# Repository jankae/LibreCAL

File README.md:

# LibreCAL
**4-port, 9kHz to 6GHz eCal module for VNAs**

## Quick Start
* You can find released versions of the GUI application and the device firmware [here](https://github.com/jankae/LibreCAL/releases).
* You do *not* need the LibreCAL-GUI if you are controlling the device manually, via a script or through the [LibreVNA-GUI](https://github.com/jankae/LibreVNA).
* If you would like to try out the newest features, the compiled versions of each commit can be found [here](https://github.com/jankae/LibreCAL/actions) (but keep in mind that some features might be unstable or incomplete).
* Please see the [user manual](Documentation/manual.pdf) for details of operation.
* If you would like to control the LibreCAL with a script, see the [SCPI API](Documentation/SCPI_API.pdf).

## Factory calibration
* All LibreCAL devices are preprogrammed with individually measured factory calibration coefficients (if you build one yourself, you need a way to measure them)
* These coefficients are important, without them the LibreCAL is nothing more than an ordinary RF switch matrix
* If the coefficients have been lost, you can download them [here](https://librecal.kaeberich.com/) (based on the serial number of your LibreCAL). If no coefficients for your LibreCAL are available, it could be a clone (not produced through official channels)

## Installation

All of the following steps are only required if you plan to use the LibreCAL-GUI. If you plan to control the LibreCAL manually with the buttons, through a script or the LibreVNA-GUI, there is no need to download the LibreCAL-GUI (but you should still install the udev rule on Linux systems).

### Windows
* Download the latest [Release](https://github.com/jankae/LibreCAL/releases) and unpack the zip file
* Start the included LibreCAL-GUI.exe
* No installation or driver is required, simply move the extracted folder somewhere convenient

### Ubuntu
* Download the latest [Release](https://github.com/jankae/LibreCAL/releases) and unpack the zip file
* Install the required libraries:
```console
sudo apt install libqt6widgets6 libqt6charts6 libqt6svg6
```
* Install the udev rule (otherwise you don't have the permissions to access the USB device):
```console
wget https://raw.githubusercontent.com/jankae/LibreCAL/main/Software/52-LibreCAL.rules
sudo cp 52-LibreCAL.rules /etc/udev/rules.d
```
* Either reboot or reload the udev rules manually:
```console
sudo udevadm control --reload-rules
sudo udevadm trigger
```
* You can now start GUI:
```console
cd $UNPACKED_ZIP_FOLDER$
./LibreCAL-GUI
```

### MacOS
* Download the latest [Release](https://github.com/jankae/LibreCAL/releases)
  * If you are using MacOS 14+ use the release with `latest` in the name.
  * If you are using MacOS >13.7 use the release with  `13.7` in the name.
* Unpack the zip file and move LibreCAL-GUI.app to your `/Applications` folder.
* Start LibreCAL-GUI.app and add a security exception to allow the Mac to run the app with an "untrusted" signing key.
* Launch app again.

## How does it work?
The LibreCAL is just a switch-matrix with additional options to terminate each port into an open, short or 50 Ohm connection:

While the blockdiagram is small and simple, the tricky part of any eCal module is repeatability. The LibreCAL contains an integrated heater and temperature sensor to keep the critical parts at a constant temperature during operation. Furthermore, high quality SMA connectors are used to ensure good return loss.

The coefficients of the calibration standards are stored in standard touchstone format on the device. They must be measured and written once after assembling the PCB and housing.

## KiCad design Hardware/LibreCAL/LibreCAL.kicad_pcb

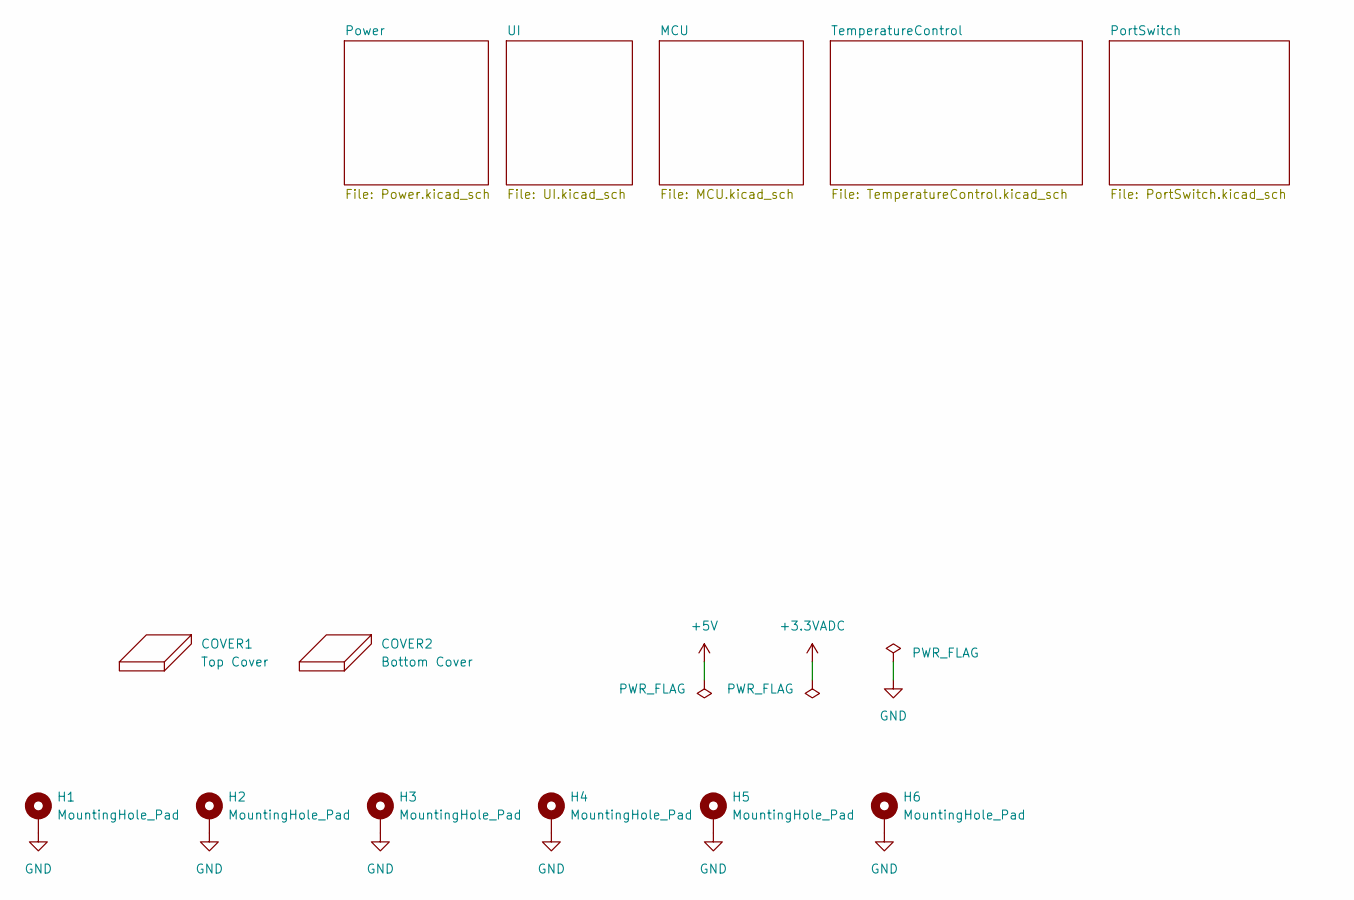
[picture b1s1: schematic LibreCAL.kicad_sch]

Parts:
COVER1: Top Cover; TopCover; LCSC_Part NA
COVER2: Bottom Cover; BottomCover; LCSC_Part NA
H1, H2, H3, H4, H5, H6: MountingHole_Pad; MountingHole_3.2mm_M3_ISO14580_Pad_TopBottom; LCSC_Part NA

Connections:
GND: H1.1, H2.1, H3.1, H4.1, H5.1, H6.1; also elsewhere on the board

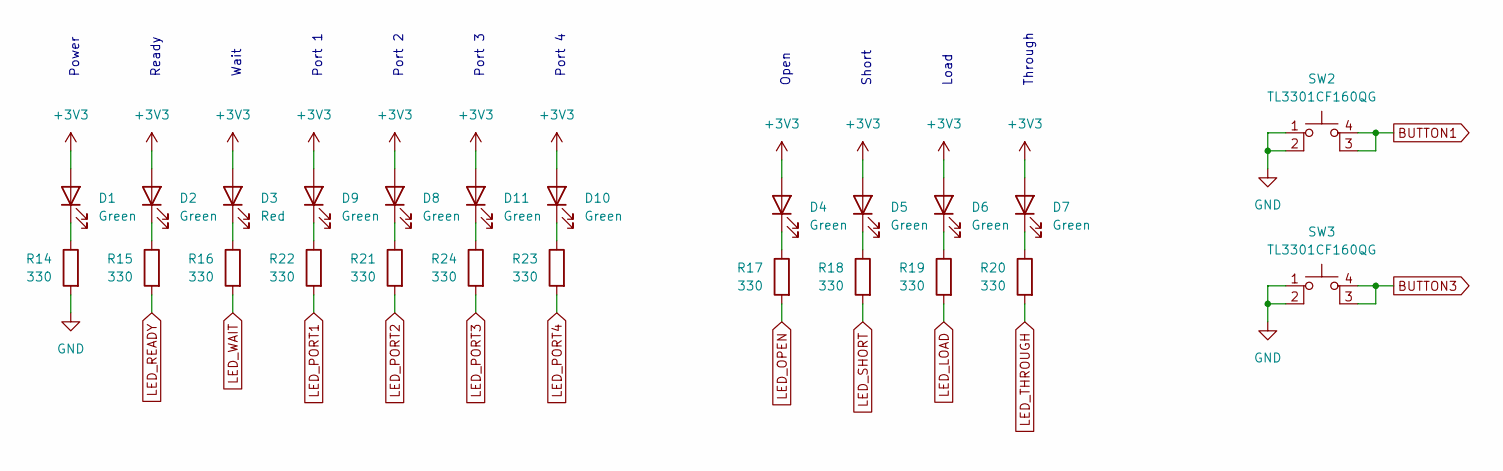
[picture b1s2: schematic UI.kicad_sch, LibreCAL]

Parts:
D1, D2, D4, D5, D6, D7, D8, D9, D10, D11: Green; LED_0603_1608Metric; LCSC_Part C72043
D3: Red; LED_0603_1608Metric; LCSC_Part C93128
R14, R15, R16, R17, R18, R19, R20, R21, R22, R23, R24: 330; R_0402_1005Metric; LCSC_Part C25104
SW2, SW3: TL3301CF160QG; TL3301C-J; LCSC_Part C273522

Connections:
+3V3: D1.2 (A), D2.2 (A), D3.2 (A), D4.2 (A), D5.2 (A), D6.2 (A), D7.2 (A), D8.2 (A), D9.2 (A), D10.2 (A), D11.2 (A); also elsewhere on the board
BUTTON1: SW2.3 (K), SW2.4 (A); also elsewhere on the board
BUTTON3: SW3.3 (K), SW3.4 (A); also elsewhere on the board
GND: R14.2, SW2.1, SW2.2, SW3.1, SW3.2; also elsewhere on the board
LED_LOAD: R19.2; also elsewhere on the board
LED_OPEN: R17.2; also elsewhere on the board
LED_PORT1: R22.2; also elsewhere on the board
LED_PORT2: R21.2; also elsewhere on the board
LED_PORT3: R24.2; also elsewhere on the board
LED_PORT4: R23.2; also elsewhere on the board
LED_READY: R15.2; also elsewhere on the board
LED_SHORT: R18.2; also elsewhere on the board
LED_THROUGH: R20.2; also elsewhere on the board
LED_WAIT: R16.2; also elsewhere on the board
unnamed: D1.1 (K), R14.1
unnamed: D2.1 (K), R15.1
unnamed: D3.1 (K), R16.1
unnamed: D4.1 (K), R17.1
unnamed: D5.1 (K), R18.1
unnamed: D6.1 (K), R19.1
unnamed: D7.1 (K), R20.1
unnamed: D8.1 (K), R21.1
unnamed: D9.1 (K), R22.1
unnamed: D10.1 (K), R23.1
unnamed: D11.1 (K), R24.1

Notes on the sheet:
Short
Port 3
Power
Port 1
Through
Wait
Port 2
Ready
Open
Load
Port 4

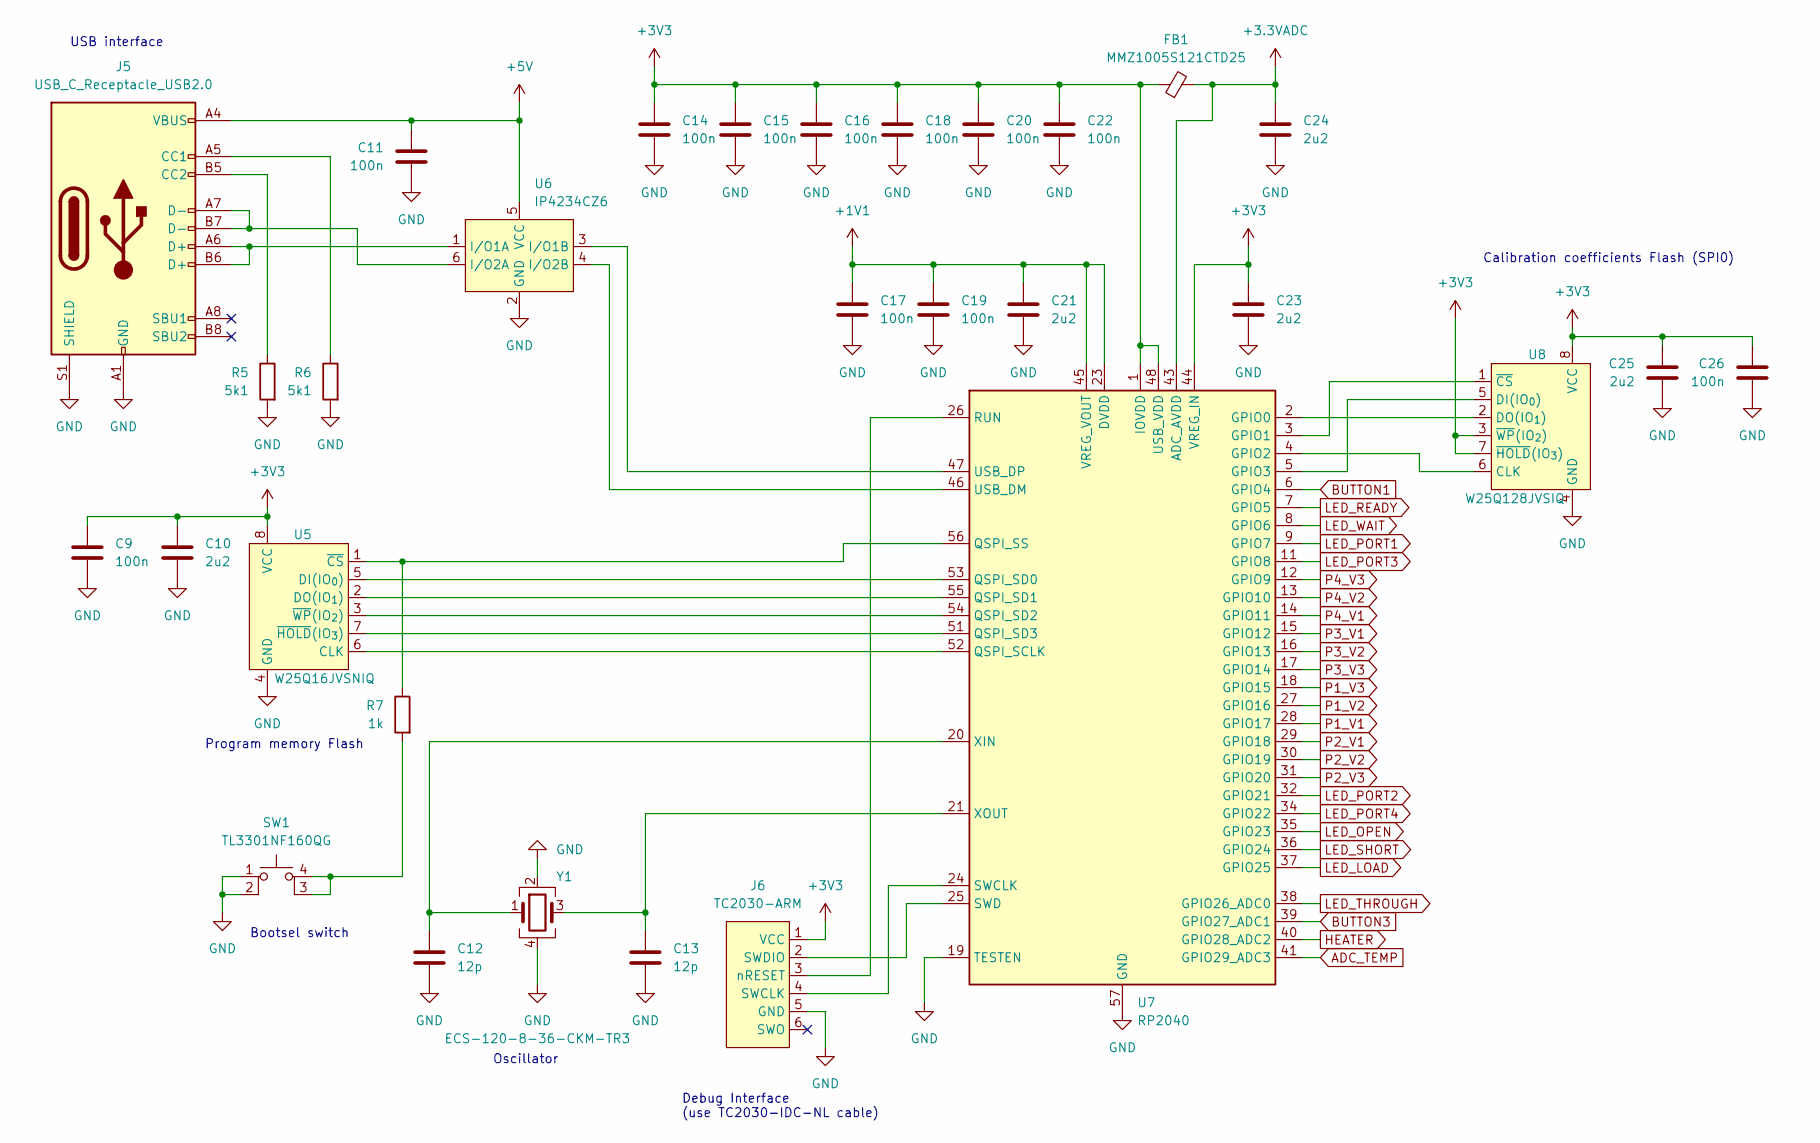
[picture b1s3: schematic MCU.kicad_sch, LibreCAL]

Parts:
C9, C11, C14, C15, C16, C17, C18, C19, C20, C22, C26: 100n; C_0402_1005Metric; LCSC_Part C307331
C10, C21, C23, C24, C25: 2u2; C_0402_1005Metric; LCSC_Part C307418
C12, C13: 12p; C_0402_1005Metric; LCSC_Part C76948
FB1: MMZ1005S121CTD25; L_0402_1005Metric; LCSC_Part C404693
J5: USB_C_Receptacle_USB2.0; USB_C_Receptacle_HRO_TYPE-C-31-M-12; LCSC_Part C165948
J6: TC2030-ARM; Tag-Connect_TC2030-IDC-NL_2x03_P1.27mm_Vertical; LCSC_Part NA
R5, R6: 5k1; R_0402_1005Metric; LCSC_Part C105872
R7: 1k; R_0402_1005Metric; LCSC_Part C106235
SW1: TL3301NF160QG; TL3301N-J; LCSC_Part C273527
U5: W25Q16JVSNIQ; SOIC-8_3.9x4.9mm_P1.27mm; LCSC_Part C115407
U6: IP4234CZ6; SOT-23-6; LCSC_Part C455086
U7: RP2040; LCSC_Part C2040
U8: W25Q128JVSIQ; SOIC-8_5.23x5.23mm_P1.27mm; LCSC_Part C115407
Y1: ECS-120-8-36-CKM-TR3; Crystal_SMD_2520-4Pin_2.5x2.0mm; LCSC_Part C5349079

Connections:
+1V1: C17.1, C19.1, C21.1, U7.23 (DVDD), U7.45 (VREG_VOUT), U7.50 (DVDD)
+3.3VADC: C24.1, FB1.2, U7.43 (ADC_AVDD); also elsewhere on the board
+3V3: C9.1, C10.1, C14.1, C15.1, C16.1, C18.1, C20.1, C22.1, C23.1, C25.1, C26.1, FB1.1, J6.1 (VCC), U5.8 (VCC), U7.1 (IOVDD), U7.10 (IOVDD), U7.22 (IOVDD), U7.33 (IOVDD), U7.42 (IOVDD), U7.44 (VREG_IN), U7.48 (USB_VDD), U7.49 (IOVDD), U8.3 (~WP(IO_{2})), U8.7 (~HOLD(IO_{3})), U8.8 (VCC); also elsewhere on the board
+5V: C11.1, J5.A4 (VBUS), J5.A9 (VBUS), J5.B4 (VBUS), J5.B9 (VBUS), U6.5 (VCC); also elsewhere on the board
ADC_TEMP: U7.41 (GPIO29_ADC3); also elsewhere on the board
BUTTON1: U7.6 (GPIO4); also elsewhere on the board
BUTTON3: U7.39 (GPIO27_ADC1); also elsewhere on the board
GND: C9.2, C10.2, C11.2, C12.2, C13.2, C14.2, C15.2, C16.2, C17.2, C18.2, C19.2, C20.2, C21.2, C22.2, C23.2, C24.2, C25.2, C26.2, J5.A1 (GND), J5.A12 (GND), J5.B1 (GND), J5.B12 (GND), J5.S1 (SHIELD), J6.5 (GND), R5.2, R6.2, SW1.1, SW1.2, U5.4 (GND), U6.2 (GND), U7.19 (TESTEN), U7.57 (GND), U8.4 (GND), Y1.2, Y1.4; also elsewhere on the board
HEATER: U7.40 (GPIO28_ADC2); also elsewhere on the board
LED_LOAD: U7.37 (GPIO25); also elsewhere on the board
LED_OPEN: U7.35 (GPIO23); also elsewhere on the board
LED_PORT1: U7.9 (GPIO7); also elsewhere on the board
LED_PORT2: U7.32 (GPIO21); also elsewhere on the board
LED_PORT3: U7.11 (GPIO8); also elsewhere on the board
LED_PORT4: U7.34 (GPIO22); also elsewhere on the board
LED_READY: U7.7 (GPIO5); also elsewhere on the board
LED_SHORT: U7.36 (GPIO24); also elsewhere on the board
LED_THROUGH: U7.38 (GPIO26_ADC0); also elsewhere on the board
LED_WAIT: U7.8 (GPIO6); also elsewhere on the board
unnamed: J5.A5 (CC1), R6.1
unnamed: J5.B5 (CC2), R5.1
unnamed: J6.4 (SWCLK), U7.24 (SWCLK)
unnamed: J6.2 (SWDIO), U7.25 (SWD)
unnamed: J6.3 (nRESET), U7.26 (RUN)
unnamed: R7.2, SW1.3 (K), SW1.4 (A)
unnamed: U5.6 (CLK), U7.52 (QSPI_SCLK)
unnamed: U5.5 (DI(IO_{0})), U7.53 (QSPI_SD0)
unnamed: U5.2 (DO(IO_{1})), U7.55 (QSPI_SD1)
unnamed: R7.1, U5.1 (~CS), U7.56 (QSPI_SS)
unnamed: U5.7 (~HOLD(IO_{3})), U7.51 (QSPI_SD3)
unnamed: U5.3 (~WP(IO_{2})), U7.54 (QSPI_SD2)
unnamed: J5.A6 (D+), J5.B6 (D+), U6.1 (I/O1A)
unnamed: U6.3 (I/O1B), U7.47 (USB_DP)
unnamed: J5.A7 (D-), J5.B7 (D-), U6.6 (I/O2A)
unnamed: U6.4 (I/O2B), U7.46 (USB_DM)
unnamed: U7.2 (GPIO0), U8.2 (DO(IO_{1}))
unnamed: U7.3 (GPIO1), U8.1 (~CS)
unnamed: U7.4 (GPIO2), U8.6 (CLK)
unnamed: U7.5 (GPIO3), U8.5 (DI(IO_{0}))
unnamed: C12.1, U7.20 (XIN), Y1.1
unnamed: C13.1, U7.21 (XOUT), Y1.3
P1_V1: U7.28 (GPIO17); also elsewhere on the board
P1_V2: U7.27 (GPIO16); also elsewhere on the board
P1_V3: U7.18 (GPIO15); also elsewhere on the board
P2_V1: U7.29 (GPIO18); also elsewhere on the board
P2_V2: U7.30 (GPIO19); also elsewhere on the board
P2_V3: U7.31 (GPIO20); also elsewhere on the board
P3_V1: U7.15 (GPIO12); also elsewhere on the board
P3_V2: U7.16 (GPIO13); also elsewhere on the board
P3_V3: U7.17 (GPIO14); also elsewhere on the board
P4_V1: U7.14 (GPIO11); also elsewhere on the board
P4_V2: U7.13 (GPIO10); also elsewhere on the board
P4_V3: U7.12 (GPIO9); also elsewhere on the board

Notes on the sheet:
USB interface
Oscillator
Program memory Flash
Debug Interface (use TC2030-IDC-NL cable)
Bootsel switch
Calibration coefficients Flash (SPI0)

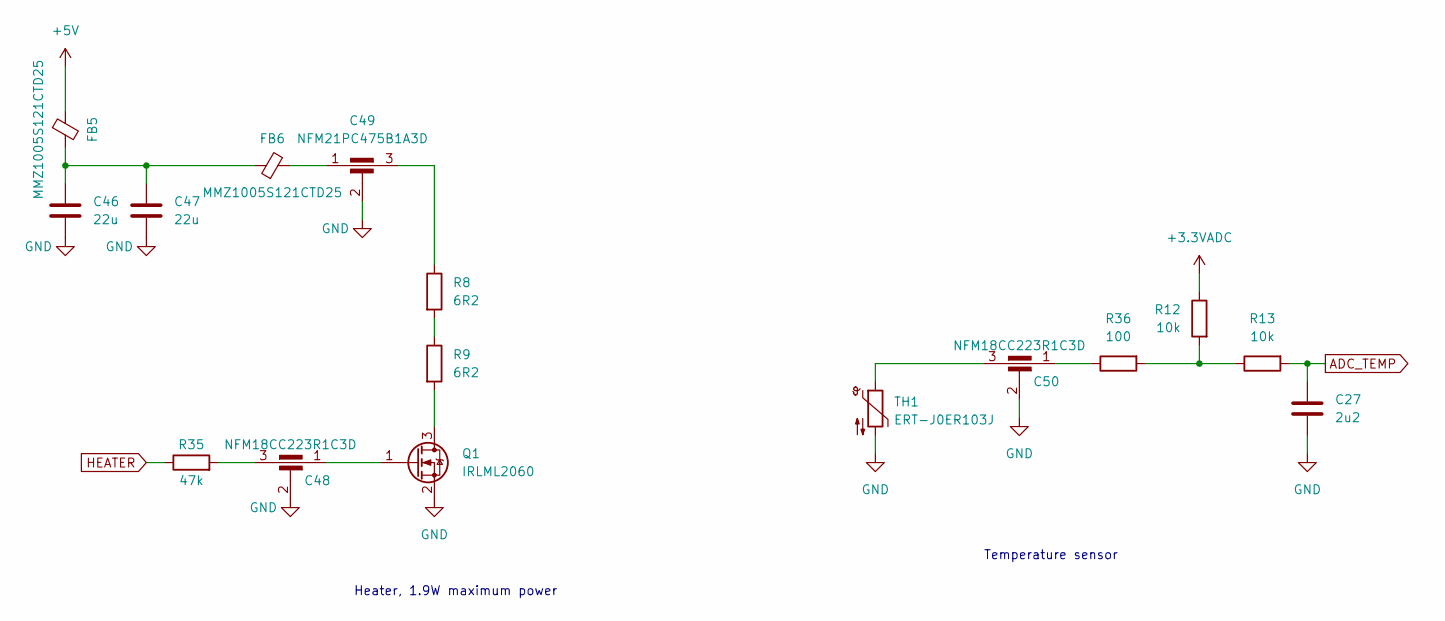
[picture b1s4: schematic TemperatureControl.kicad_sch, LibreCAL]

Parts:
C27: 2u2; C_0402_1005Metric; LCSC_Part C307418
C46, C47: 22u; C_0805_2012Metric; LCSC_Part C45783
C48, C50: NFM18CC223R1C3D; NFM18CC; LCSC_Part C98102
C49: NFM21PC475B1A3D; NFM21PC; LCSC_Part C96293
FB5, FB6: MMZ1005S121CTD25; L_0402_1005Metric; LCSC_Part C404693
Q1: IRLML2060; SOT-23; LCSC_Part C67275
R8, R9: 6R2; R_2512_6332Metric; LCSC_Part C147196
R12, R13: 10k; R_0402_1005Metric; LCSC_Part C723353
R35: 47k; R_0402_1005Metric; LCSC_Part C144757
R36: 100; R_0402_1005Metric; LCSC_Part C25076
TH1: ERT-J0ER103J; R_0402_1005Metric; LCSC_Part C153027

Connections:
+3.3VADC: R12.1; also elsewhere on the board
+5V: FB5.1; also elsewhere on the board
ADC_TEMP: C27.1, R13.2; also elsewhere on the board
GND: C27.2, C46.2, C47.2, C48.2, C49.2, C50.2, Q1.2 (S), TH1.2; also elsewhere on the board
HEATER: R35.1; also elsewhere on the board
unnamed: C46.1, C47.1, FB5.2, FB6.1
unnamed: C48.3, R35.2
unnamed: C49.1, FB6.2
unnamed: C49.3, R8.1
unnamed: C50.1, R36.1
unnamed: C50.3, TH1.1
unnamed: Q1.3 (D), R9.2
unnamed: C48.1, Q1.1 (G)
unnamed: R8.2, R9.1
unnamed: R12.2, R13.1, R36.2

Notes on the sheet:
Temperature sensor
Heater, 1.9W maximum power

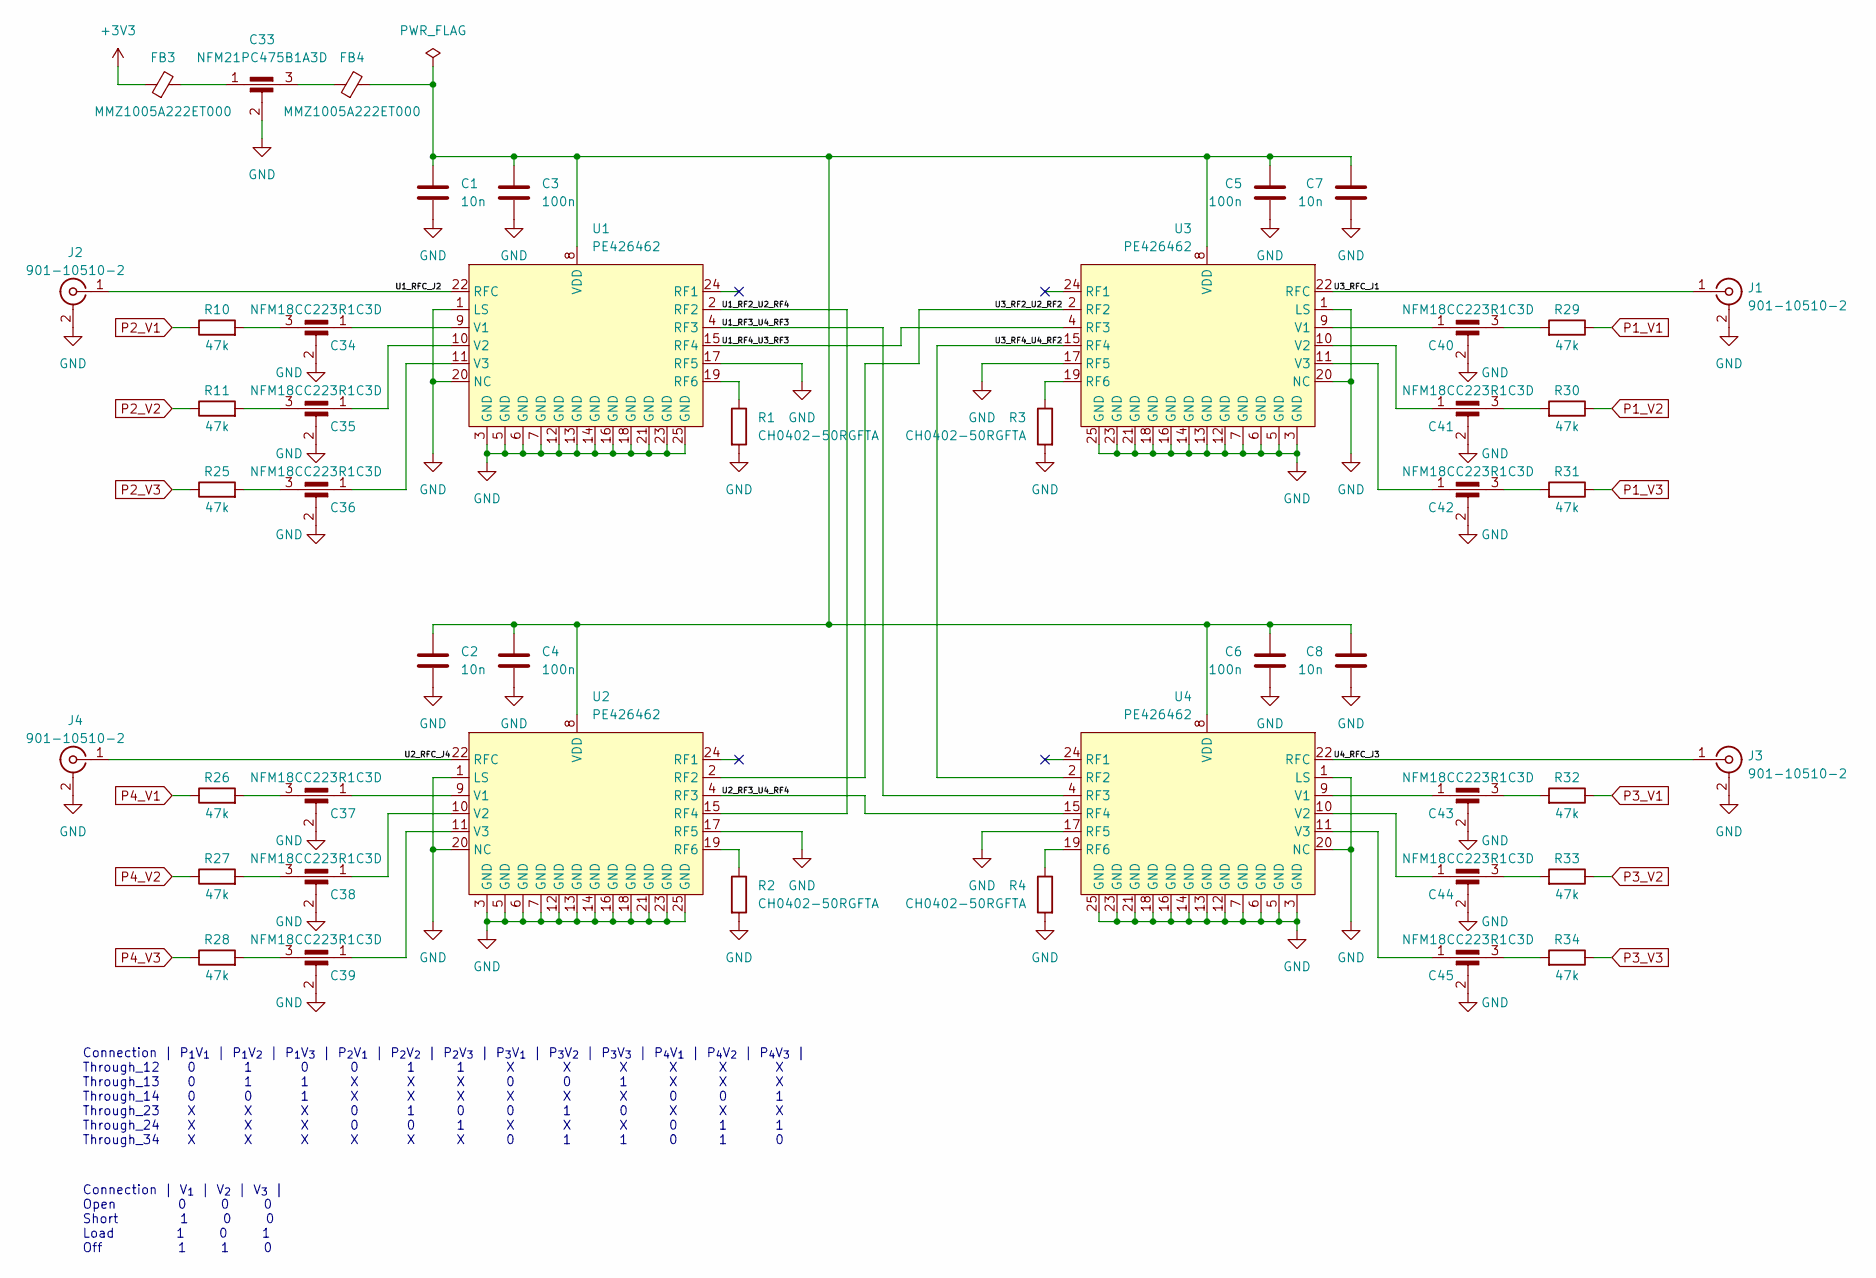
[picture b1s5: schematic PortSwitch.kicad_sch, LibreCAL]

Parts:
C1, C2, C7, C8: 10n; C_0402_1005Metric; LCSC_Part C15195
C3, C4, C5, C6: 100n; C_0402_1005Metric; LCSC_Part C307331
C33: NFM21PC475B1A3D; NFM21PC; LCSC_Part C96293
C34, C35, C36, C37, C38, C39, C40, C41, C42, C43, C44, C45: NFM18CC223R1C3D; NFM18CC; LCSC_Part C98102
FB3, FB4: MMZ1005A222ET000; L_0402_1005Metric; LCSC_Part C275411
J1, J2, J3, J4: 901-10510-2; LCSC_Part C3172623
R1, R2, R3, R4: CH0402-50RGFTA; R_0402_1005Metric; LCSC_Part C5349731
R10, R11, R25, R26, R27, R28, R29, R30, R31, R32, R33, R34: 47k; R_0402_1005Metric; LCSC_Part C144757
U1, U2, U3, U4: PE426462; QFN-24-1EP_4x4mm_P0.5mm_EP2.7x2.7mm; LCSC_Part C5349078

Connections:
+3V3: FB3.1; also elsewhere on the board
/PortSwitch/U1_RF2_U2_RF4: U1.2 (RF2), U2.15 (RF4)
/PortSwitch/U1_RF3_U4_RF3: U1.4 (RF3), U4.4 (RF3)
/PortSwitch/U1_RF4_U3_RF3: U1.15 (RF4), U3.4 (RF3)
/PortSwitch/U1_RFC_J2: J2.1 (In), U1.22 (RFC)
/PortSwitch/U2_RF3_U4_RF4: U2.4 (RF3), U4.15 (RF4)
/PortSwitch/U2_RFC_J4: J4.1 (In), U2.22 (RFC)
/PortSwitch/U3_RF2_U2_RF2: U2.2 (RF2), U3.2 (RF2)
/PortSwitch/U3_RF4_U4_RF2: U3.15 (RF4), U4.2 (RF2)
/PortSwitch/U3_RFC_J1: J1.1 (In), U3.22 (RFC)
/PortSwitch/U4_RFC_J3: J3.1 (In), U4.22 (RFC)
GND: C1.2, C2.2, C3.2, C4.2, C5.2, C6.2, C7.2, C8.2, C33.2, C34.2, C35.2, C36.2, C37.2, C38.2, C39.2, C40.2, C41.2, C42.2, C43.2, C44.2, C45.2, J1.2 (Ext), J1.3 (Ext), J1.4 (Ext), J1.5 (Ext), J1.6 (Ext), J1.7 (Ext), J2.2 (Ext), J2.3 (Ext), J2.4 (Ext), J2.5 (Ext), J2.6 (Ext), J2.7 (Ext), J3.2 (Ext), J3.3 (Ext), J3.4 (Ext), J3.5 (Ext), J3.6 (Ext), J3.7 (Ext), J4.2 (Ext), J4.3 (Ext), J4.4 (Ext), J4.5 (Ext), J4.6 (Ext), J4.7 (Ext), R1.2, R2.2, R3.2, R4.2, U1.1 (LS), U1.3 (GND), U1.5 (GND), U1.6 (GND), U1.7 (GND), U1.12 (GND), U1.13 (GND), U1.14 (GND), U1.16 (GND), U1.17 (RF5), U1.18 (GND), U1.20 (NC), U1.21 (GND), U1.23 (GND), U1.25 (GND), U2.1 (LS), U2.3 (GND), U2.5 (GND), U2.6 (GND), U2.7 (GND), U2.12 (GND), U2.13 (GND), U2.14 (GND), U2.16 (GND), U2.17 (RF5), U2.18 (GND), U2.20 (NC), U2.21 (GND), U2.23 (GND), U2.25 (GND), U3.1 (LS), U3.3 (GND), U3.5 (GND), U3.6 (GND), U3.7 (GND), U3.12 (GND), U3.13 (GND), U3.14 (GND), U3.16 (GND), U3.17 (RF5), U3.18 (GND), U3.20 (NC), U3.21 (GND), U3.23 (GND), U3.25 (GND), U4.1 (LS), U4.3 (GND), U4.5 (GND), U4.6 (GND), U4.7 (GND), U4.12 (GND), U4.13 (GND), U4.14 (GND), U4.16 (GND), U4.17 (RF5), U4.18 (GND), U4.20 (NC), U4.21 (GND), U4.23 (GND), U4.25 (GND); also elsewhere on the board
unnamed: C33.1, FB3.2
unnamed: C33.3, FB4.1
unnamed: C34.3, R10.2
unnamed: C35.3, R11.2
unnamed: C36.3, R25.2
unnamed: C37.3, R26.2
unnamed: C38.3, R27.2
unnamed: C39.3, R28.2
unnamed: C40.3, R29.2
unnamed: C41.3, R30.2
unnamed: C42.3, R31.2
unnamed: C43.3, R32.2
unnamed: C44.3, R33.2
unnamed: C45.3, R34.2
unnamed: R1.1, U1.19 (RF6)
unnamed: C34.1, U1.9 (V1)
unnamed: C35.1, U1.10 (V2)
unnamed: C36.1, U1.11 (V3)
unnamed: C1.1, C2.1, C3.1, C4.1, C5.1, C6.1, C7.1, C8.1, FB4.2, U1.8 (VDD), U2.8 (VDD), U3.8 (VDD), U4.8 (VDD)
unnamed: R2.1, U2.19 (RF6)
unnamed: C37.1, U2.9 (V1)
unnamed: C38.1, U2.10 (V2)
unnamed: C39.1, U2.11 (V3)
unnamed: R3.1, U3.19 (RF6)
unnamed: C40.1, U3.9 (V1)
unnamed: C41.1, U3.10 (V2)
unnamed: C42.1, U3.11 (V3)
unnamed: R4.1, U4.19 (RF6)
unnamed: C43.1, U4.9 (V1)
unnamed: C44.1, U4.10 (V2)
unnamed: C45.1, U4.11 (V3)
P1_V1: R29.1; also elsewhere on the board
P1_V2: R30.1; also elsewhere on the board
P1_V3: R31.1; also elsewhere on the board
P2_V1: R10.1; also elsewhere on the board
P2_V2: R11.1; also elsewhere on the board
P2_V3: R25.1; also elsewhere on the board
P3_V1: R32.1; also elsewhere on the board
P3_V2: R33.1; also elsewhere on the board
P3_V3: R34.1; also elsewhere on the board
P4_V1: R26.1; also elsewhere on the board
P4_V2: R27.1; also elsewhere on the board
P4_V3: R28.1; also elsewhere on the board

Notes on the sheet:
Connection | P_{1}V_{1} | P_{1}V_{2} | P_{1}V_{3} | P_{2}V_{1} | P_{2}V_{2} | P_{2}V_{3} | P_{3}V_{1} | P_{3}V_{2} | P_{3}V_{3} | P_{4}V_{1} | P_{4}V_{2} | P_{4}V_{3} | Through_12 0 1 0 0 1 1 X X X X X X Through_13 0 1 1 X X X 0 0 1 X X X Through_14 0 0 1 X X X X X X 0 0 1 Through_23 X X X 0 1 0 0 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
Connection | V_{1} | V_{2} | V_{3} | Open 0 0 0 Short 1 0 0 Load 1 0 1 Off 1 1 0

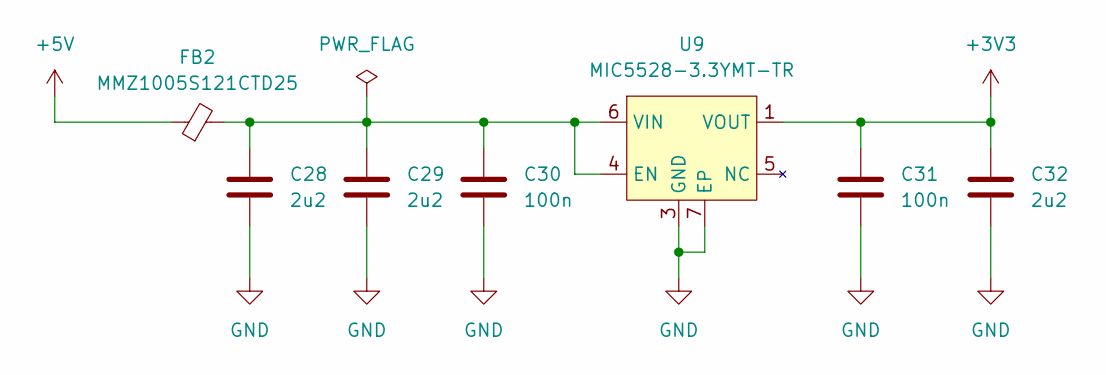
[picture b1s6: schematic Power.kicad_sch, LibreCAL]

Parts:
C28, C29, C32: 2u2; C_0402_1005Metric; LCSC_Part C307418
C30, C31: 100n; C_0402_1005Metric; LCSC_Part C307331
FB2: MMZ1005S121CTD25; L_0402_1005Metric; LCSC_Part C404693
U9: MIC5528-3.3YMT-TR; DFN-6-1EP_1.2x1.2mm_P0.4mm_EP0.3x0.94mm; LCSC_Part C622490

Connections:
+3V3: C31.1, C32.1, U9.1 (VOUT), U9.2 (VOUT); also elsewhere on the board
+5V: FB2.1; also elsewhere on the board
GND: C28.2, C29.2, C30.2, C31.2, C32.2, U9.3 (GND), U9.7 (EP); also elsewhere on the board
unnamed: C28.1, C29.1, C30.1, FB2.2, U9.4 (EN), U9.6 (VIN)

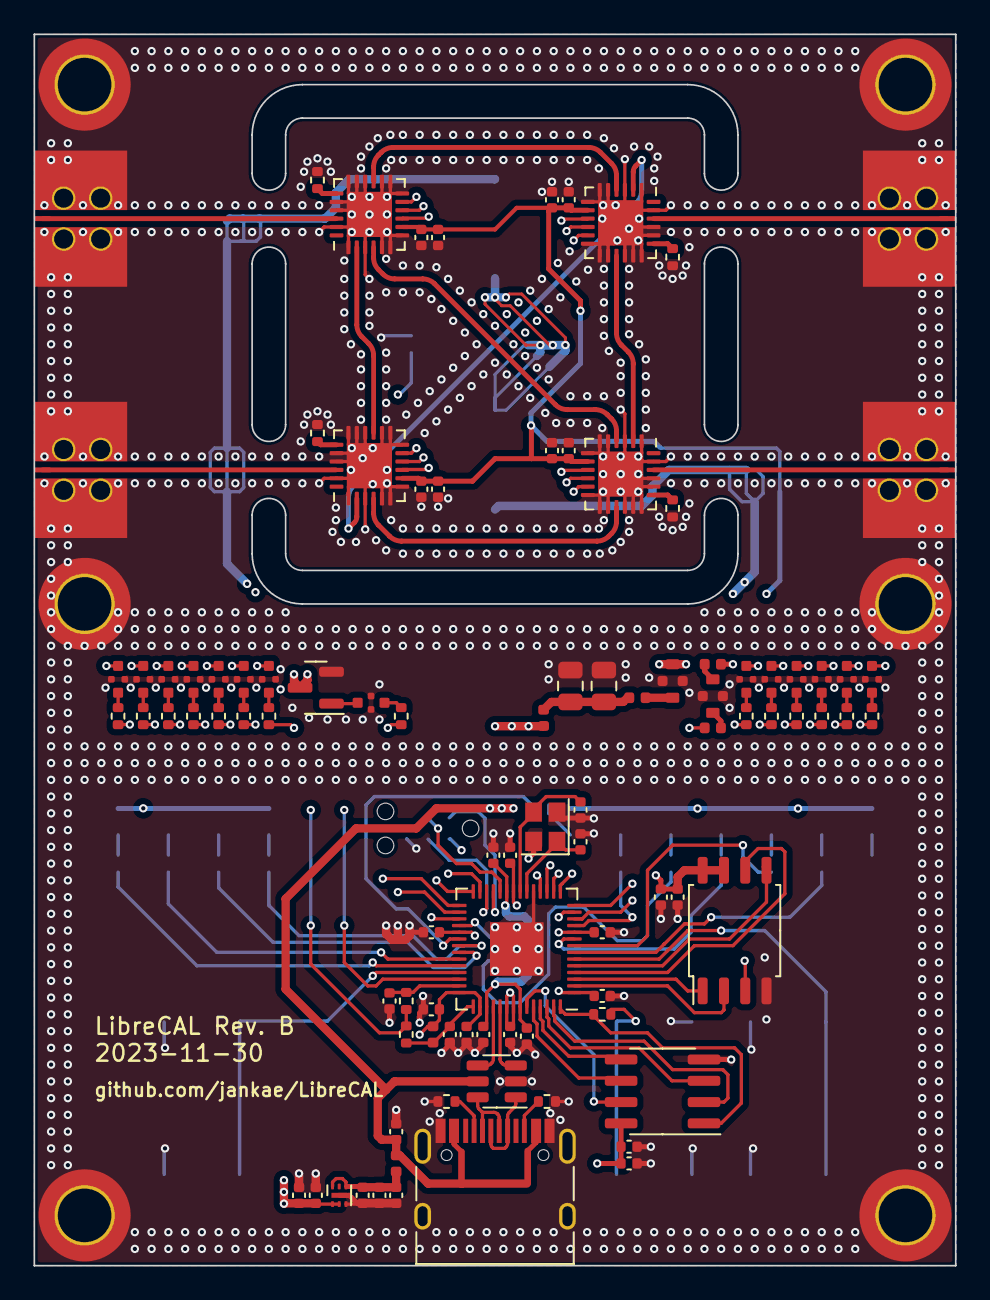
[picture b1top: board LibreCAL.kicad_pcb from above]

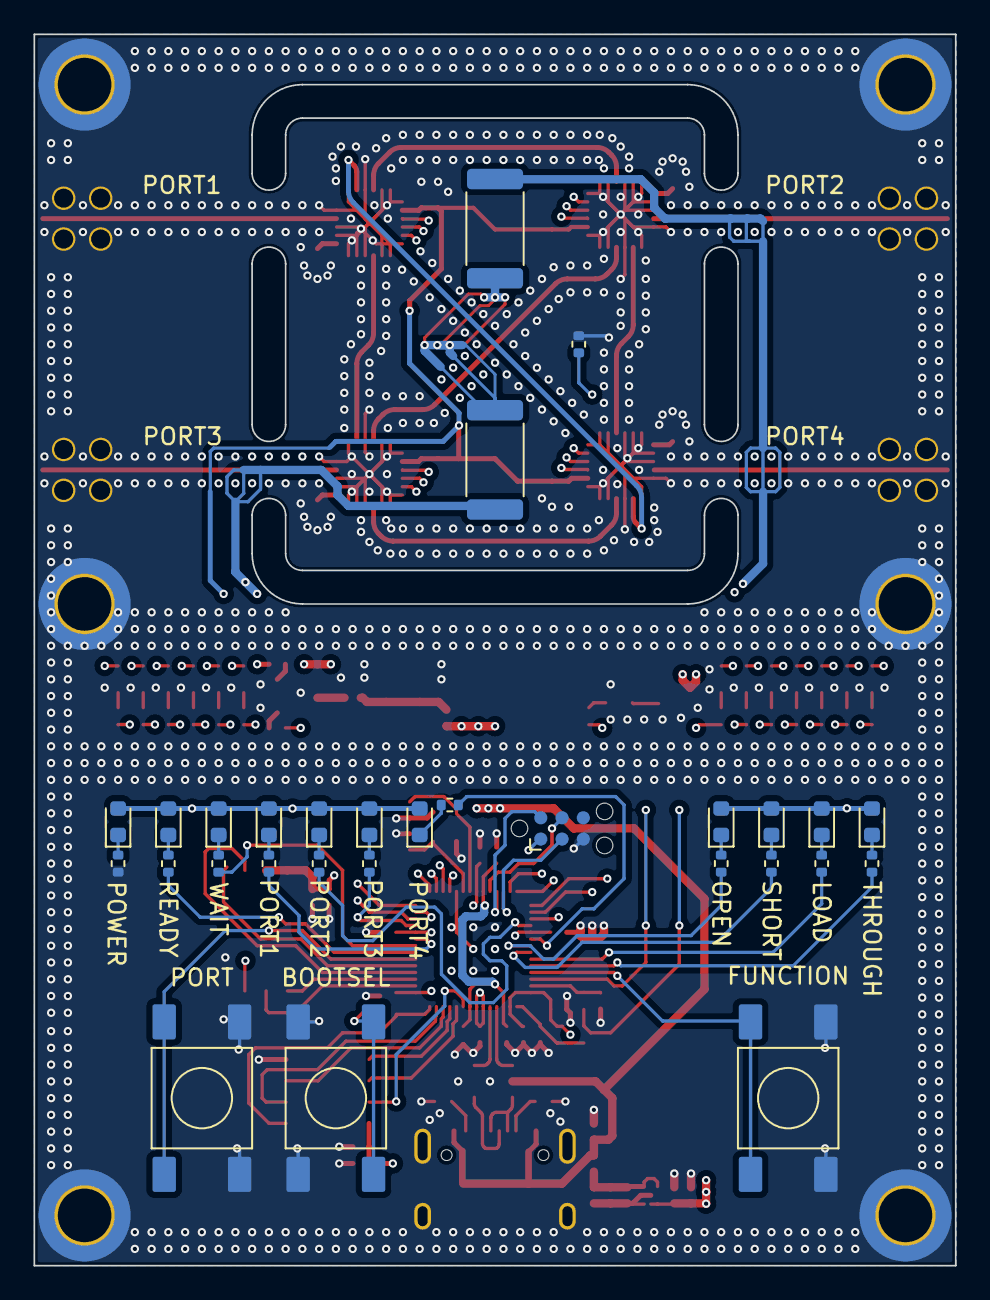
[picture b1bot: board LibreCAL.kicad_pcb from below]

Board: 4 copper layers, 55.0 x 73.5 mm, 132 parts (30 on the bottom side), 116 nets.

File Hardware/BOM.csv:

"Source:","/home/jan/Projekte/LibreCAL/Hardware/LibreCAL/LibreCAL.kicad_sch"
"Date:","Do 30 Nov 2023 18:18:11 CET"
"Tool:","Eeschema 7.0.8-7.0.8~ubuntu22.04.1"
"Generator:","/usr/share/kicad/plugins/bom_csv_grouped_by_value_with_fp.py"
"Component Count:","123"
"Ref","Qnty","Value","Cmp name","Footprint","Description","Vendor","DNP"
"C1, C2, C7, C8","4","10n","C","Capacitor_SMD:C_0402_1005Metric","Unpolarized capacitor","",""
"C3, C4, C5, C6, C9, C11, C14, C15, C16, C17, C18, C19, C20, C22, C26, C30, C31","17","100n","C","Capacitor_SMD:C_0402_1005Metric","Unpolarized capacitor","",""
"C10, C21, C23, C24, C25, C27, C28, C29, C32","9","2u2","C","Capacitor_SMD:C_0402_1005Metric","Unpolarized capacitor","",""
"C12, C13","2","12p","C","Capacitor_SMD:C_0402_1005Metric","Unpolarized capacitor","",""
"C33, C49","2","NFM21PC475B1A3D","C_Feedthrough","LibreCAL:NFM21PC","Feedthrough capacitor","",""
"C34, C35, C36, C37, C38, C39, C40, C41, C42, C43, C44, C45, C48, C50","14","NFM18CC223R1C3D","C_Feedthrough","LibreCAL:NFM18CC","Feedthrough capacitor","",""
"C46, C47","2","22u","C","Capacitor_SMD:C_0805_2012Metric","Unpolarized capacitor","",""
"D1, D2, D4, D5, D6, D7, D8, D9, D10, D11","10","Green","LED","LED_SMD:LED_0603_1608Metric","Light emitting diode","",""
"D3","1","Red","LED","LED_SMD:LED_0603_1608Metric","Light emitting diode","",""
"FB1, FB2, FB5, FB6","4","MMZ1005S121CTD25","FerriteBead_Small","Inductor_SMD:L_0402_1005Metric","Ferrite bead, small symbol","",""
"FB3, FB4","2","MMZ1005A222ET000","FerriteBead_Small","Inductor_SMD:L_0402_1005Metric","Ferrite bead, small symbol","",""
"J1, J2, J3, J4","4","901-10510-2","901-10510-2","LibreCAL:901-10510-2","High quality SMA connector, Amphenol","",""
"J5","1","USB_C_Receptacle_USB2.0","USB_C_Receptacle_USB2.0","Connector_USB:USB_C_Receptacle_HRO_TYPE-C-31-M-12","USB 2.0-only Type-C Receptacle connector","",""
"Q1","1","IRLML2060","IRLML2060","Package_TO_SOT_SMD:SOT-23","1.2A Id, 60V Vds, 480mOhm Rds, N-Channel HEXFET Power MOSFET, SOT-23","",""
"R1, R2, R3, R4","4","CH0402-50RGFTA","R","Resistor_SMD:R_0402_1005Metric","Resistor","",""
"R5, R6","2","5k1","R","Resistor_SMD:R_0402_1005Metric","Resistor","",""
"R7","1","1k","R","Resistor_SMD:R_0402_1005Metric","Resistor","",""
"R8, R9","2","6R2","R","Resistor_SMD:R_2512_6332Metric","Resistor","",""
"R10, R11, R25, R26, R27, R28, R29, R30, R31, R32, R33, R34, R35","13","47k","R","Resistor_SMD:R_0402_1005Metric","Resistor","",""
"R12, R13","2","10k","R","Resistor_SMD:R_0402_1005Metric","Resistor","",""
"R14, R15, R16, R17, R18, R19, R20, R21, R22, R23, R24","11","330","R","Resistor_SMD:R_0402_1005Metric","Resistor","",""
"R36","1","100","R","Resistor_SMD:R_0402_1005Metric","Resistor","",""
"SW1","1","TL3301NF160QG","SW_MEC_5E","LibreCAL:TL3301N-J","MEC 5E single pole normally-open tactile switch","",""
"SW2, SW3","2","TL3301CF160QG","SW_MEC_5E","LibreCAL:TL3301C-J","MEC 5E single pole normally-open tactile switch","",""
"TH1","1","ERT-J0ER103J","Thermistor_NTC","Resistor_SMD:R_0402_1005Metric","Temperature dependent resistor, negative temperature coefficient","",""
"U1, U2, U3, U4","4","PE426462","PE426462","Package_DFN_QFN:QFN-24-1EP_4x4mm_P0.5mm_EP2.7x2.7mm","","",""
"U5","1","W25Q16JVSNIQ","W25Q16JVSNIQ","Package_SO:SOIC-8_3.9x4.9mm_P1.27mm","","",""
"U6","1","IP4234CZ6","IP4234CZ6","Package_TO_SOT_SMD:SOT-23-6","","",""
"U7","1","RP2040","RP2040","LibreCAL:RP2040","A microcontroller by Raspberry Pi","",""
"U8","1","W25Q128JVSIQ","W25Q16JVSNIQ","Package_SO:SOIC-8_5.23x5.23mm_P1.27mm","","",""
"U9","1","MIC5528-3.3YMT-TR","MIC5528","LibreCAL:DFN-6-1EP_1.2x1.2mm_P0.4mm_EP0.3x0.94mm","LDO","",""
"Y1","1","ECS-120-8-36-CKM-TR3","Crystal_GND24","Crystal:Crystal_SMD_2520-4Pin_2.5x2.0mm","Four pin crystal, GND on pins 2 and 4","",""
